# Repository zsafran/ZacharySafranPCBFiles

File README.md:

# ZacharySafranPCBFiles

The purpose of this repository is to showcase the PCB designs that I have worked with and those that I have created myself.

The folder 1_AntennaBrd_ANDESITE contains the .sch and .brd files for the antenna mounting PCB that I mention in my resume. I worked on designing this PCB with a research engineer in my lab. My main contributions to the design were to make sure that the mounting holes for the antennas, and sun sensor were in the right spot by referencing a CAD model of the satellite and to use MATLAB simulations to get an idea of how the shape of the PCB's ground plane would affect the monopole/dipole antennas's impedance.

The majority of the time I worked in the Space Technology Lab during the 2017 summer was spent on assembling and testing PCBs for the pico-satellite nodes that make up the ANDESITE satellite swarm. The .sch and .brd files for these PCBs are in the 2_Node_PCB_ANDESITE and 3_Node_SolarPanels_ANDESITE folders respectively. The main Node_PCB is a 4 layer PCB and the  Node_SolarPanels PCB is a 2 layer PCB. While I was not involved with designing either of these PCBs, working with them exposed me to more complex PCB layout and design techniques like using Restrict layer polygons to prevent ground plane copper from being laid in a specific area.

The only PCBs that I have designed and ordered completely by myself were two breakout boards for an altimeter sensor and an accelerometer sensor. I designed the altimeter PCB in EAGLE and the accelerometer PCB in Altium.

# Photos

## Satellite Pictures

<center></center>

A few of the full assembled satellite nodes.
&nbsp;

<center></center>

A partially assembled node satellite circuit board.
&nbsp;

## Testing Sensors Photo

<center></center>

My altimeter breakout board (top left) and my accelerometer breakout board (top right) can be see being tested in this picture.

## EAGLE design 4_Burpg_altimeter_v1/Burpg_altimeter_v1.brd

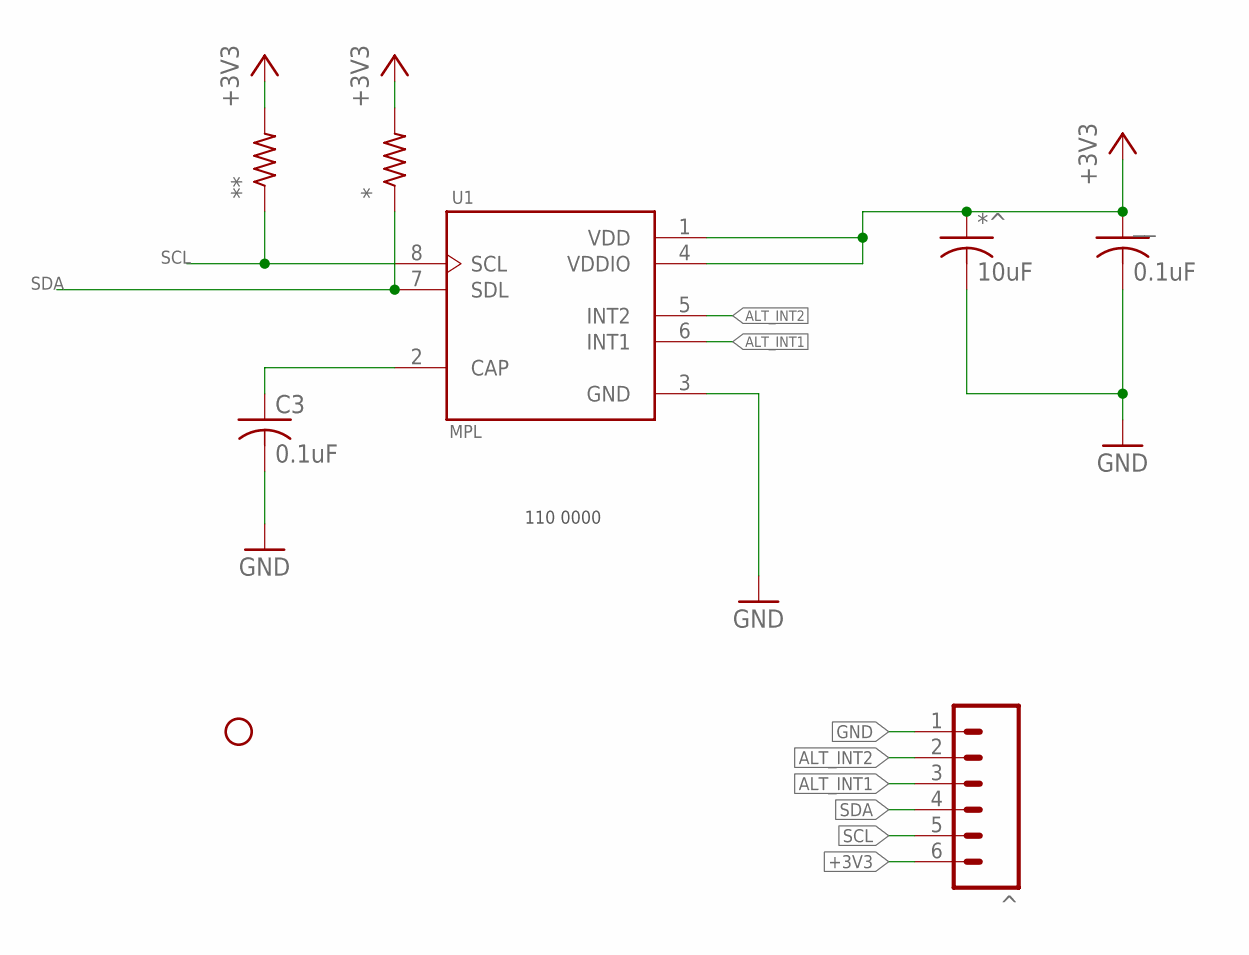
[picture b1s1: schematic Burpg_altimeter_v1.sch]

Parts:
*: R-US_R0603; R0603
**: R-US_R0603; R0603
*^: 10uF; C0603K
C3: 0.1uF; C0603K
U1: MPL; PSON125P300X500X120-8N
^: M06SILK_FEMALE_PTH; 1X06
_: #4_philip; STAND-OFF
__: 0.1uF; C0603K

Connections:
+3V3: *.2, **.2, *^.1, U1.1 (VDD), U1.4 (VDDIO), ^.6, __.1
ALT_INT1: U1.6 (INT1), ^.3
ALT_INT2: U1.5 (INT2), ^.2
GND: *^.2, C3.2, U1.3 (GND), ^.1, __.2
unnamed: C3.1, U1.2 (CAP)
SCL: **.1, U1.8 (SCL), ^.5
SDA: *.1, U1.7 (SDL), ^.4

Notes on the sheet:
110 0000

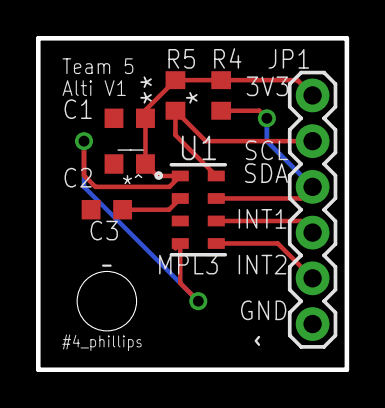
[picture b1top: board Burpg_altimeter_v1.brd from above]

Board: 2 copper layers, 17.1 x 18.4 mm, 8 parts (0 on the bottom side), 7 nets.

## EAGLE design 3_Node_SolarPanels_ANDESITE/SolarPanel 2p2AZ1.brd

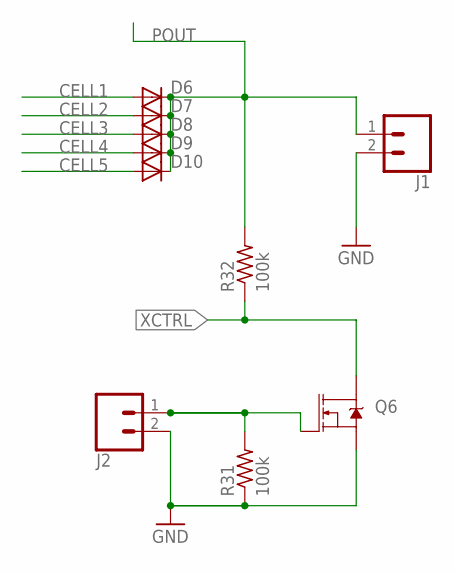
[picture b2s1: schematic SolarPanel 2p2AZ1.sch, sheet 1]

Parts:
D6, D7, D8, D9, D10: DIODE-SOD123; SOD123
J1, J2: CONN_02; 1X02
Q6: MOSFET-NCH-BSS138; SOT23-3
R31, R32: 100k; R0603

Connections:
CELL1: D6.A; also elsewhere on the board
CELL2: D7.A; also elsewhere on the board
CELL3: D8.A; also elsewhere on the board
CELL4: D9.A; also elsewhere on the board
CELL5: D10.A; also elsewhere on the board
GND: J1.2, J2.2, Q6.2 (S), R31.1; also elsewhere on the board
unnamed: J2.1, Q6.1 (G), R31.2
POUT: D6.C, D7.C, D8.C, D9.C, D10.C, J1.1, R32.2
XCTRL: Q6.3 (D), R32.1; also elsewhere on the board

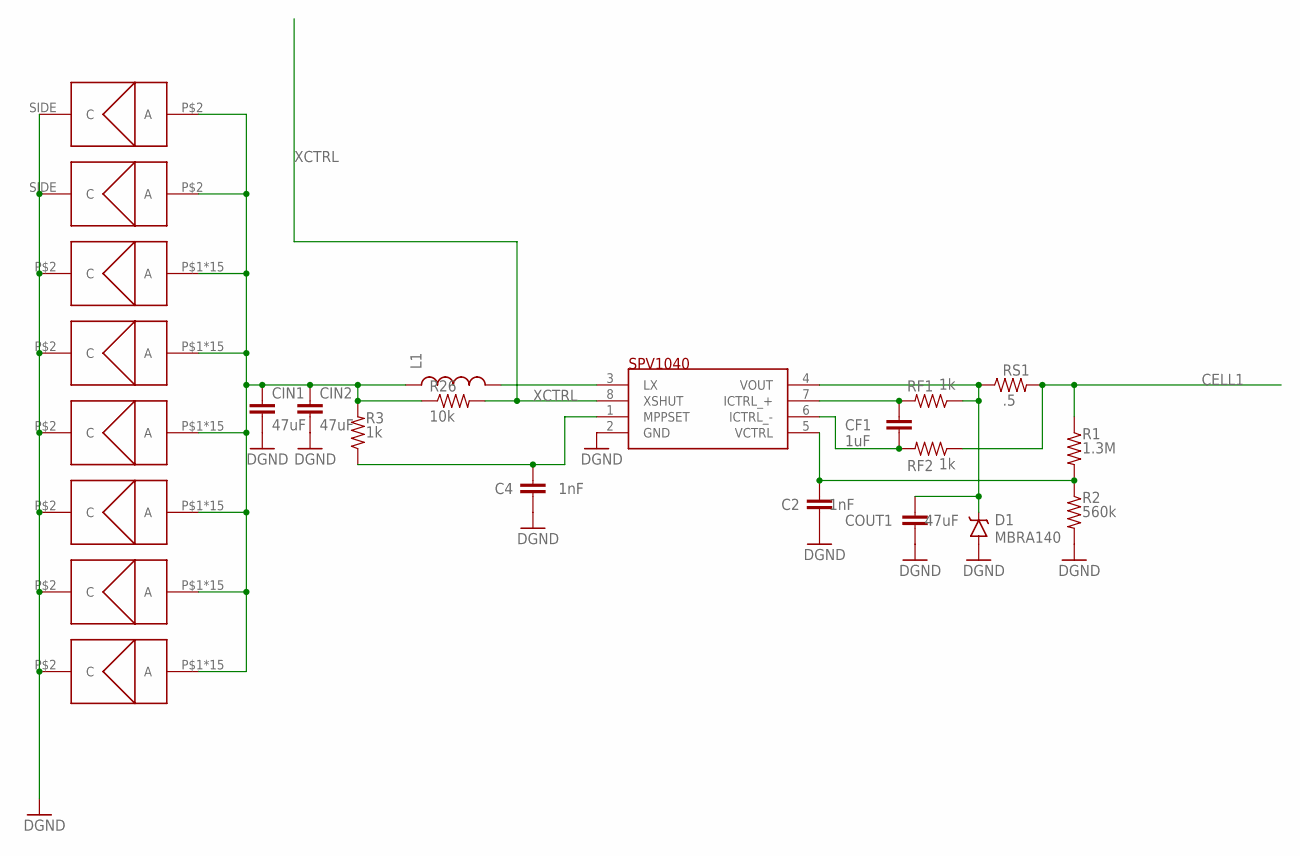
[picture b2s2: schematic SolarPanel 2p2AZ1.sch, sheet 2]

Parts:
C2, C4: 1nF; 0603-CAP
CF1: 1uF; 0603-CAP
CIN1, CIN2: 47uF; 1206
COUT1: 47uF; 1206
D1: MBRA140; SMA-DIODE
L1: INDUCTOR1210; 1210
R1: 1.3M; 0603-RES
R2: 560k; 0603-RES
R3: 1k; 0603-RES
R26: 10k; 0603-RES
RF1, RF2: 1k; 0603-RES
RS1: .5; 0603-RES
U$11, U$12, U$13, U$14, U$16, U$17: TASC_VIA
U$15: SPV1040; TSSOP8
U$18, U$19: TASC

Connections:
CELL1: R1.1, RF2.1, RS1.2; also elsewhere on the board
GND: C2.2, C4.2, CIN1.2, CIN2.2, COUT1.2, D1.A, R2.2, U$11.P$2 (C), U$12.P$2 (C), U$13.P$2 (C), U$14.P$2 (C), U$15.2 (GND), U$16.P$2 (C), U$17.P$2 (C), U$18.SIDE (C), U$19.SIDE (C); also elsewhere on the board
unnamed: CIN1.1, CIN2.1, L1.1, R3.2, R26.1, U$11.P$1 (A), U$11.P$3 (A), U$11.P$4 (A), U$11.P$5 (A), U$11.P$6 (A), U$11.P$7 (A), U$11.P$8 (A), U$11.P$9 (A), U$11.P$10 (A), U$11.P$11 (A), U$11.P$12 (A), U$11.P$13 (A), U$11.P$14 (A), U$11.P$15 (A), U$11.P$16 (A), U$12.P$1 (A), U$12.P$3 (A), U$12.P$4 (A), U$12.P$5 (A), U$12.P$6 (A), U$12.P$7 (A), U$12.P$8 (A), U$12.P$9 (A), U$12.P$10 (A), U$12.P$11 (A), U$12.P$12 (A), U$12.P$13 (A), U$12.P$14 (A), U$12.P$15 (A), U$12.P$16 (A), U$13.P$1 (A), U$13.P$3 (A), U$13.P$4 (A), U$13.P$5 (A), U$13.P$6 (A), U$13.P$7 (A), U$13.P$8 (A), U$13.P$9 (A), U$13.P$10 (A), U$13.P$11 (A), U$13.P$12 (A), U$13.P$13 (A), U$13.P$14 (A), U$13.P$15 (A), U$13.P$16 (A), U$14.P$1 (A), U$14.P$3 (A), U$14.P$4 (A), U$14.P$5 (A), U$14.P$6 (A), U$14.P$7 (A), U$14.P$8 (A), U$14.P$9 (A), U$14.P$10 (A), U$14.P$11 (A), U$14.P$12 (A), U$14.P$13 (A), U$14.P$14 (A), U$14.P$15 (A), U$14.P$16 (A), U$16.P$1 (A), U$16.P$3 (A), U$16.P$4 (A), U$16.P$5 (A), U$16.P$6 (A), U$16.P$7 (A), U$16.P$8 (A), U$16.P$9 (A), U$16.P$10 (A), U$16.P$11 (A), U$16.P$12 (A), U$16.P$13 (A), U$16.P$14 (A), U$16.P$15 (A), U$16.P$16 (A), U$17.P$1 (A), U$17.P$3 (A), U$17.P$4 (A), U$17.P$5 (A), U$17.P$6 (A), U$17.P$7 (A), U$17.P$8 (A), U$17.P$9 (A), U$17.P$10 (A), U$17.P$11 (A), U$17.P$12 (A), U$17.P$13 (A), U$17.P$14 (A), U$17.P$15 (A), U$17.P$16 (A), U$18.P$2 (A), U$19.P$2 (A)
unnamed: C2.1, R1.2, R2.1, U$15.5 (VCTRL)
unnamed: CF1.1, RF1.2, U$15.7 (ICTRL_+)
unnamed: CF1.2, RF2.2, U$15.6 (ICTRL_-)
unnamed: COUT1.1, D1.C, RF1.1, RS1.1, U$15.4 (VOUT)
unnamed: L1.2, U$15.3 (LX)
unnamed: C4.1, R3.1, U$15.1 (MPPSET)
XCTRL: R26.2, U$15.8 (XSHUT); also elsewhere on the board

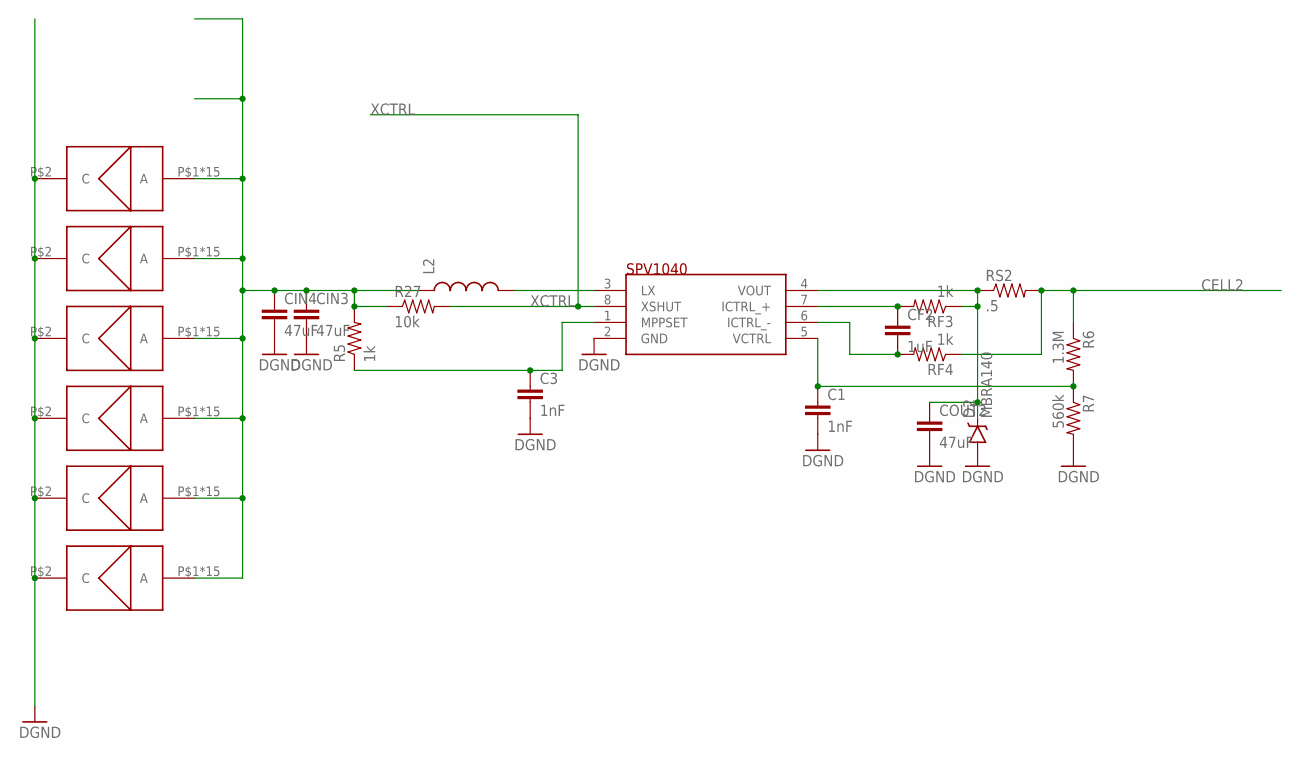
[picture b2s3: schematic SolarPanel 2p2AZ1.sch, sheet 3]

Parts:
C1, C3: 1nF; 0603-CAP
CF2: 1uF; 0603-CAP
CIN3, CIN4: 47uF; 1206
COUT2: 47uF; 1206
D2: MBRA140; SMA-DIODE
L2: INDUCTOR1210; 1210
R5: 1k; 0603-RES
R6: 1.3M; 0603-RES
R7: 560k; 0603-RES
R27: 10k; 0603-RES
RF3, RF4: 1k; 0603-RES
RS2: .5; 0603-RES
U$1, U$2, U$3, U$4, U$6, U$7: TASC_VIA
U$5: SPV1040; TSSOP8

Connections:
CELL2: R6.1, RF4.1, RS2.2; also elsewhere on the board
GND: C1.2, C3.2, CIN3.2, CIN4.2, COUT2.2, D2.A, R7.2, U$1.P$2 (C), U$2.P$2 (C), U$3.P$2 (C), U$4.P$2 (C), U$5.2 (GND), U$6.P$2 (C), U$7.P$2 (C); also elsewhere on the board
unnamed: CIN3.1, CIN4.1, L2.1, R5.2, R27.1, U$1.P$1 (A), U$1.P$3 (A), U$1.P$4 (A), U$1.P$5 (A), U$1.P$6 (A), U$1.P$7 (A), U$1.P$8 (A), U$1.P$9 (A), U$1.P$10 (A), U$1.P$11 (A), U$1.P$12 (A), U$1.P$13 (A), U$1.P$14 (A), U$1.P$15 (A), U$1.P$16 (A), U$2.P$1 (A), U$2.P$3 (A), U$2.P$4 (A), U$2.P$5 (A), U$2.P$6 (A), U$2.P$7 (A), U$2.P$8 (A), U$2.P$9 (A), U$2.P$10 (A), U$2.P$11 (A), U$2.P$12 (A), U$2.P$13 (A), U$2.P$14 (A), U$2.P$15 (A), U$2.P$16 (A), U$3.P$1 (A), U$3.P$3 (A), U$3.P$4 (A), U$3.P$5 (A), U$3.P$6 (A), U$3.P$7 (A), U$3.P$8 (A), U$3.P$9 (A), U$3.P$10 (A), U$3.P$11 (A), U$3.P$12 (A), U$3.P$13 (A), U$3.P$14 (A), U$3.P$15 (A), U$3.P$16 (A), U$4.P$1 (A), U$4.P$3 (A), U$4.P$4 (A), U$4.P$5 (A), U$4.P$6 (A), U$4.P$7 (A), U$4.P$8 (A), U$4.P$9 (A), U$4.P$10 (A), U$4.P$11 (A), U$4.P$12 (A), U$4.P$13 (A), U$4.P$14 (A), U$4.P$15 (A), U$4.P$16 (A), U$6.P$1 (A), U$6.P$3 (A), U$6.P$4 (A), U$6.P$5 (A), U$6.P$6 (A), U$6.P$7 (A), U$6.P$8 (A), U$6.P$9 (A), U$6.P$10 (A), U$6.P$11 (A), U$6.P$12 (A), U$6.P$13 (A), U$6.P$14 (A), U$6.P$15 (A), U$6.P$16 (A), U$7.P$1 (A), U$7.P$3 (A), U$7.P$4 (A), U$7.P$5 (A), U$7.P$6 (A), U$7.P$7 (A), U$7.P$8 (A), U$7.P$9 (A), U$7.P$10 (A), U$7.P$11 (A), U$7.P$12 (A), U$7.P$13 (A), U$7.P$14 (A), U$7.P$15 (A), U$7.P$16 (A)
unnamed: C3.1, R5.1, U$5.1 (MPPSET)
unnamed: C1.1, R6.2, R7.1, U$5.5 (VCTRL)
unnamed: CF2.1, RF3.2, U$5.7 (ICTRL_+)
unnamed: CF2.2, RF4.2, U$5.6 (ICTRL_-)
unnamed: COUT2.1, D2.C, RF3.1, RS2.1, U$5.4 (VOUT)
unnamed: L2.2, U$5.3 (LX)
XCTRL: R27.2, U$5.8 (XSHUT); also elsewhere on the board

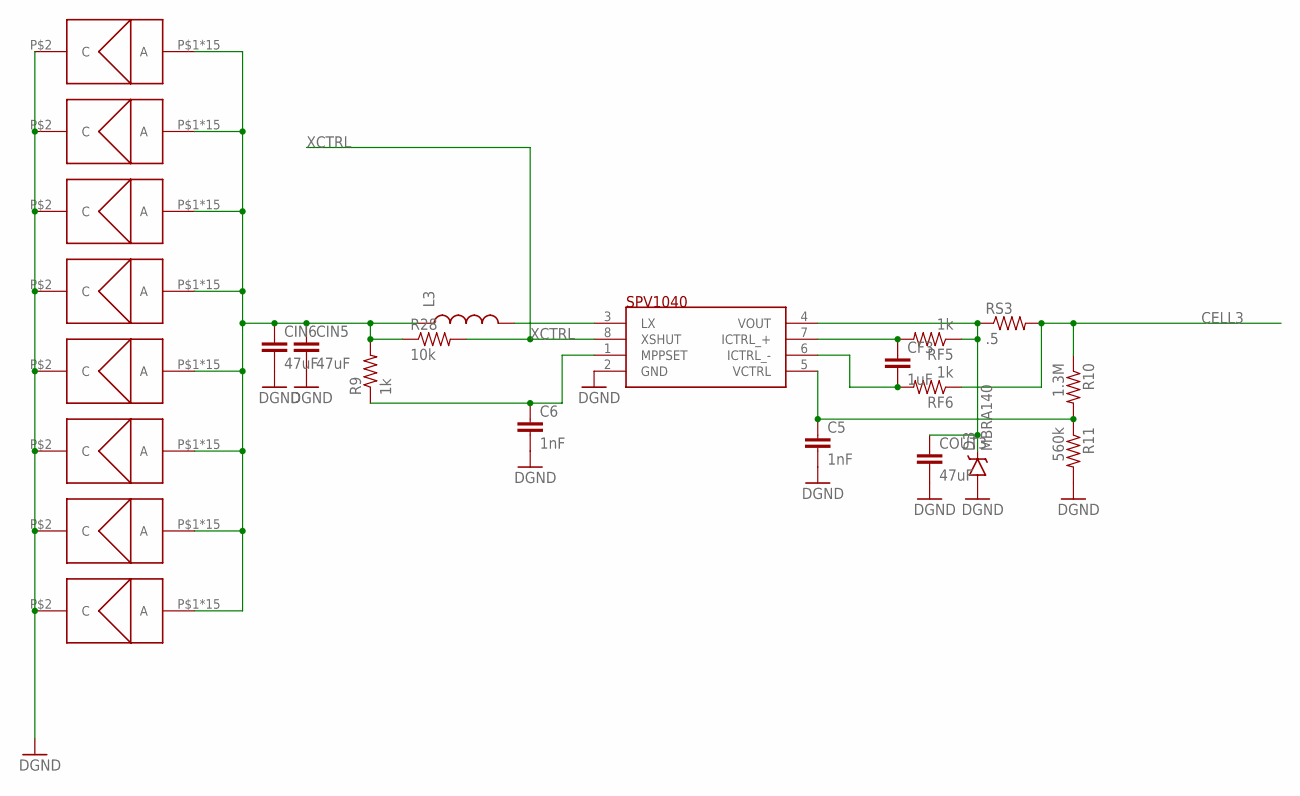
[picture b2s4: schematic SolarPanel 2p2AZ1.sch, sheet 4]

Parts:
C5, C6: 1nF; 0603-CAP
CF3: 1uF; 0603-CAP
CIN5, CIN6: 47uF; 1206
COUT3: 47uF; 1206
D3: MBRA140; SMA-DIODE
L3: INDUCTOR1210; 1210
R9: 1k; 0603-RES
R10: 1.3M; 0603-RES
R11: 560k; 0603-RES
R28: 10k; 0603-RES
RF5, RF6: 1k; 0603-RES
RS3: .5; 0603-RES
U$21, U$22, U$23, U$24, U$26, U$27, U$28, U$29: TASC_VIA
U$25: SPV1040; TSSOP8

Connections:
CELL3: R10.1, RF6.1, RS3.2; also elsewhere on the board
GND: C5.2, C6.2, CIN5.2, CIN6.2, COUT3.2, D3.A, R11.2, U$21.P$2 (C), U$22.P$2 (C), U$23.P$2 (C), U$24.P$2 (C), U$25.2 (GND), U$26.P$2 (C), U$27.P$2 (C), U$28.P$2 (C), U$29.P$2 (C); also elsewhere on the board
unnamed: CIN5.1, CIN6.1, L3.1, R9.2, R28.1, U$21.P$1 (A), U$21.P$3 (A), U$21.P$4 (A), U$21.P$5 (A), U$21.P$6 (A), U$21.P$7 (A), U$21.P$8 (A), U$21.P$9 (A), U$21.P$10 (A), U$21.P$11 (A), U$21.P$12 (A), U$21.P$13 (A), U$21.P$14 (A), U$21.P$15 (A), U$21.P$16 (A), U$22.P$1 (A), U$22.P$3 (A), U$22.P$4 (A), U$22.P$5 (A), U$22.P$6 (A), U$22.P$7 (A), U$22.P$8 (A), U$22.P$9 (A), U$22.P$10 (A), U$22.P$11 (A), U$22.P$12 (A), U$22.P$13 (A), U$22.P$14 (A), U$22.P$15 (A), U$22.P$16 (A), U$23.P$1 (A), U$23.P$3 (A), U$23.P$4 (A), U$23.P$5 (A), U$23.P$6 (A), U$23.P$7 (A), U$23.P$8 (A), U$23.P$9 (A), U$23.P$10 (A), U$23.P$11 (A), U$23.P$12 (A), U$23.P$13 (A), U$23.P$14 (A), U$23.P$15 (A), U$23.P$16 (A), U$24.P$1 (A), U$24.P$3 (A), U$24.P$4 (A), U$24.P$5 (A), U$24.P$6 (A), U$24.P$7 (A), U$24.P$8 (A), U$24.P$9 (A), U$24.P$10 (A), U$24.P$11 (A), U$24.P$12 (A), U$24.P$13 (A), U$24.P$14 (A), U$24.P$15 (A), U$24.P$16 (A), U$26.P$1 (A), U$26.P$3 (A), U$26.P$4 (A), U$26.P$5 (A), U$26.P$6 (A), U$26.P$7 (A), U$26.P$8 (A), U$26.P$9 (A), U$26.P$10 (A), U$26.P$11 (A), U$26.P$12 (A), U$26.P$13 (A), U$26.P$14 (A), U$26.P$15 (A), U$26.P$16 (A), U$27.P$1 (A), U$27.P$3 (A), U$27.P$4 (A), U$27.P$5 (A), U$27.P$6 (A), U$27.P$7 (A), U$27.P$8 (A), U$27.P$9 (A), U$27.P$10 (A), U$27.P$11 (A), U$27.P$12 (A), U$27.P$13 (A), U$27.P$14 (A), U$27.P$15 (A), U$27.P$16 (A), U$28.P$1 (A), U$28.P$3 (A), U$28.P$4 (A), U$28.P$5 (A), U$28.P$6 (A), U$28.P$7 (A), U$28.P$8 (A), U$28.P$9 (A), U$28.P$10 (A), U$28.P$11 (A), U$28.P$12 (A), U$28.P$13 (A), U$28.P$14 (A), U$28.P$15 (A), U$28.P$16 (A), U$29.P$1 (A), U$29.P$3 (A), U$29.P$4 (A), U$29.P$5 (A), U$29.P$6 (A), U$29.P$7 (A), U$29.P$8 (A), U$29.P$9 (A), U$29.P$10 (A), U$29.P$11 (A), U$29.P$12 (A), U$29.P$13 (A), U$29.P$14 (A), U$29.P$15 (A), U$29.P$16 (A)
unnamed: C6.1, R9.1, U$25.1 (MPPSET)
unnamed: C5.1, R10.2, R11.1, U$25.5 (VCTRL)
unnamed: CF3.1, RF5.2, U$25.7 (ICTRL_+)
unnamed: CF3.2, RF6.2, U$25.6 (ICTRL_-)
unnamed: COUT3.1, D3.C, RF5.1, RS3.1, U$25.4 (VOUT)
unnamed: L3.2, U$25.3 (LX)
XCTRL: R28.2, U$25.8 (XSHUT); also elsewhere on the board

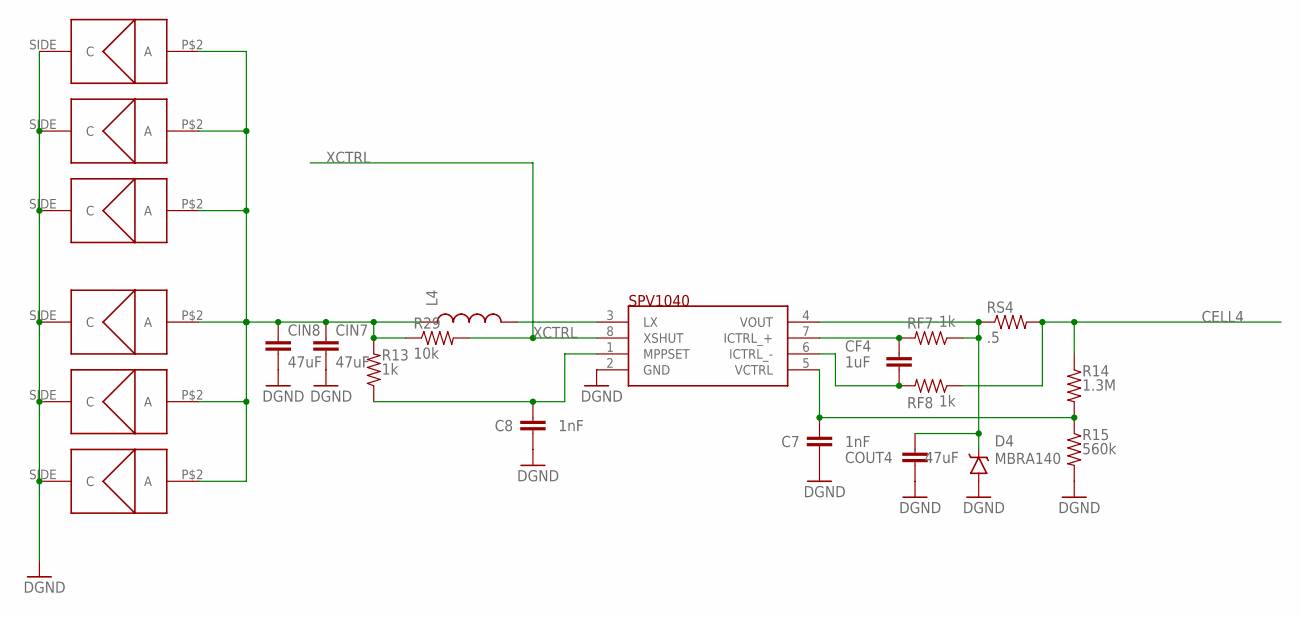
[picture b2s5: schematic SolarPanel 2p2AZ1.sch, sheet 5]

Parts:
C7, C8: 1nF; 0603-CAP
CF4: 1uF; 0603-CAP
CIN7, CIN8: 47uF; 1206
COUT4: 47uF; 1206
D4: MBRA140; SMA-DIODE
L4: INDUCTOR1210; 1210
R13: 1k; 0603-RES
R14: 1.3M; 0603-RES
R15: 560k; 0603-RES
R29: 10k; 0603-RES
RF7, RF8: 1k; 0603-RES
RS4: .5; 0603-RES
U$33, U$34, U$36, U$37, U$38, U$39: TASC
U$35: SPV1040; TSSOP8

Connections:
CELL4: R14.1, RF8.1, RS4.2; also elsewhere on the board
GND: C7.2, C8.2, CIN7.2, CIN8.2, COUT4.2, D4.A, R15.2, U$33.SIDE (C), U$34.SIDE (C), U$35.2 (GND), U$36.SIDE (C), U$37.SIDE (C), U$38.SIDE (C), U$39.SIDE (C); also elsewhere on the board
unnamed: CIN7.1, CIN8.1, L4.1, R13.2, R29.1, U$33.P$2 (A), U$34.P$2 (A), U$36.P$2 (A), U$37.P$2 (A), U$38.P$2 (A), U$39.P$2 (A)
unnamed: C8.1, R13.1, U$35.1 (MPPSET)
unnamed: C7.1, R14.2, R15.1, U$35.5 (VCTRL)
unnamed: CF4.1, RF7.2, U$35.7 (ICTRL_+)
unnamed: CF4.2, RF8.2, U$35.6 (ICTRL_-)
unnamed: COUT4.1, D4.C, RF7.1, RS4.1, U$35.4 (VOUT)
unnamed: L4.2, U$35.3 (LX)
XCTRL: R29.2, U$35.8 (XSHUT); also elsewhere on the board

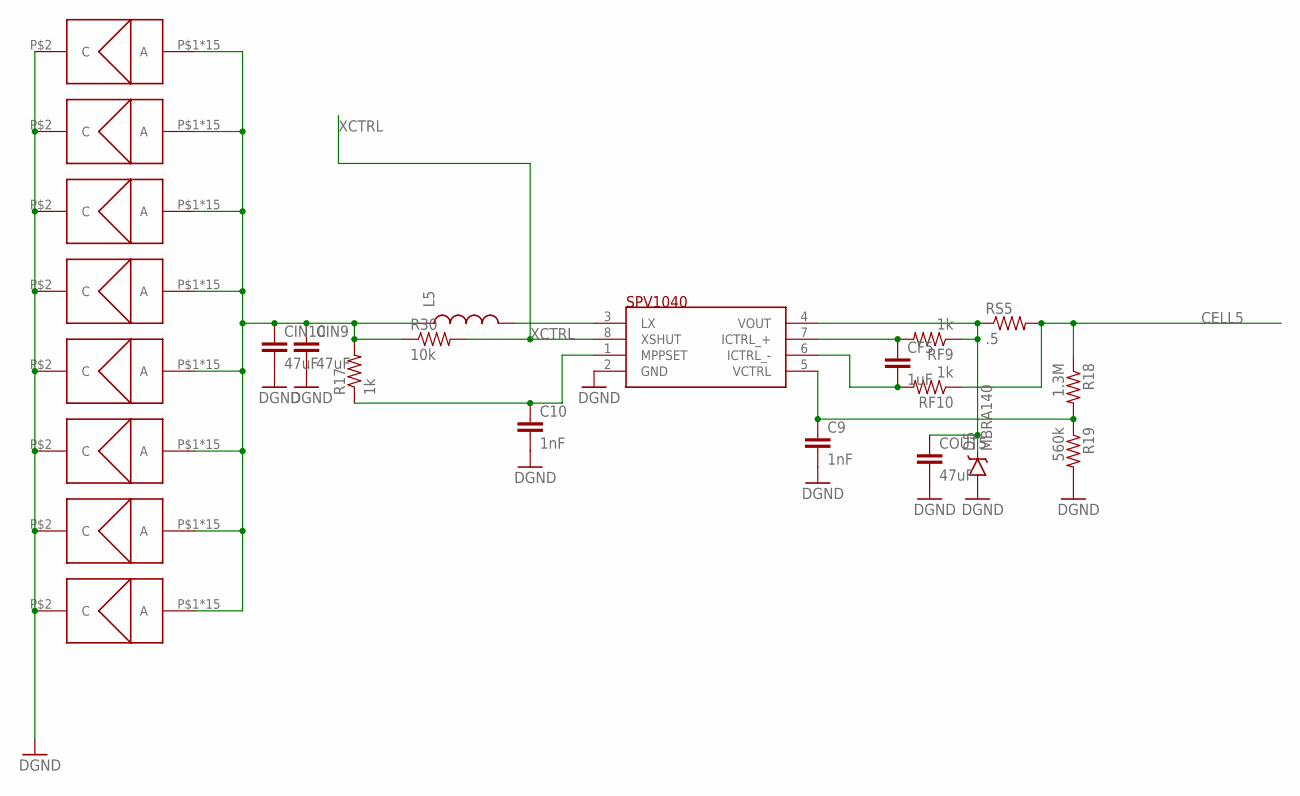
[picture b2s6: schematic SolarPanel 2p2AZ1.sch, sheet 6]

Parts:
C9, C10: 1nF; 0603-CAP
CF5: 1uF; 0603-CAP
CIN9, CIN10: 47uF; 1206
COUT5: 47uF; 1206
D5: MBRA140; SMA-DIODE
L5: INDUCTOR1210; 1210
R17: 1k; 0603-RES
R18: 1.3M; 0603-RES
R19: 560k; 0603-RES
R30: 10k; 0603-RES
RF9, RF10: 1k; 0603-RES
RS5: .5; 0603-RES
U$41, U$42, U$43, U$44, U$46, U$47, U$48, U$49: TASC_VIA
U$45: SPV1040; TSSOP8

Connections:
CELL5: R18.1, RF10.1, RS5.2; also elsewhere on the board
GND: C9.2, C10.2, CIN9.2, CIN10.2, COUT5.2, D5.A, R19.2, U$41.P$2 (C), U$42.P$2 (C), U$43.P$2 (C), U$44.P$2 (C), U$45.2 (GND), U$46.P$2 (C), U$47.P$2 (C), U$48.P$2 (C), U$49.P$2 (C); also elsewhere on the board
unnamed: CIN9.1, CIN10.1, L5.1, R17.2, R30.1, U$41.P$1 (A), U$41.P$3 (A), U$41.P$4 (A), U$41.P$5 (A), U$41.P$6 (A), U$41.P$7 (A), U$41.P$8 (A), U$41.P$9 (A), U$41.P$10 (A), U$41.P$11 (A), U$41.P$12 (A), U$41.P$13 (A), U$41.P$14 (A), U$41.P$15 (A), U$41.P$16 (A), U$42.P$1 (A), U$42.P$3 (A), U$42.P$4 (A), U$42.P$5 (A), U$42.P$6 (A), U$42.P$7 (A), U$42.P$8 (A), U$42.P$9 (A), U$42.P$10 (A), U$42.P$11 (A), U$42.P$12 (A), U$42.P$13 (A), U$42.P$14 (A), U$42.P$15 (A), U$42.P$16 (A), U$43.P$1 (A), U$43.P$3 (A), U$43.P$4 (A), U$43.P$5 (A), U$43.P$6 (A), U$43.P$7 (A), U$43.P$8 (A), U$43.P$9 (A), U$43.P$10 (A), U$43.P$11 (A), U$43.P$12 (A), U$43.P$13 (A), U$43.P$14 (A), U$43.P$15 (A), U$43.P$16 (A), U$44.P$1 (A), U$44.P$3 (A), U$44.P$4 (A), U$44.P$5 (A), U$44.P$6 (A), U$44.P$7 (A), U$44.P$8 (A), U$44.P$9 (A), U$44.P$10 (A), U$44.P$11 (A), U$44.P$12 (A), U$44.P$13 (A), U$44.P$14 (A), U$44.P$15 (A), U$44.P$16 (A), U$46.P$1 (A), U$46.P$3 (A), U$46.P$4 (A), U$46.P$5 (A), U$46.P$6 (A), U$46.P$7 (A), U$46.P$8 (A), U$46.P$9 (A), U$46.P$10 (A), U$46.P$11 (A), U$46.P$12 (A), U$46.P$13 (A), U$46.P$14 (A), U$46.P$15 (A), U$46.P$16 (A), U$47.P$1 (A), U$47.P$3 (A), U$47.P$4 (A), U$47.P$5 (A), U$47.P$6 (A), U$47.P$7 (A), U$47.P$8 (A), U$47.P$9 (A), U$47.P$10 (A), U$47.P$11 (A), U$47.P$12 (A), U$47.P$13 (A), U$47.P$14 (A), U$47.P$15 (A), U$47.P$16 (A), U$48.P$1 (A), U$48.P$3 (A), U$48.P$4 (A), U$48.P$5 (A), U$48.P$6 (A), U$48.P$7 (A), U$48.P$8 (A), U$48.P$9 (A), U$48.P$10 (A), U$48.P$11 (A), U$48.P$12 (A), U$48.P$13 (A), U$48.P$14 (A), U$48.P$15 (A), U$48.P$16 (A), U$49.P$1 (A), U$49.P$3 (A), U$49.P$4 (A), U$49.P$5 (A), U$49.P$6 (A), U$49.P$7 (A), U$49.P$8 (A), U$49.P$9 (A), U$49.P$10 (A), U$49.P$11 (A), U$49.P$12 (A), U$49.P$13 (A), U$49.P$14 (A), U$49.P$15 (A), U$49.P$16 (A)
unnamed: C10.1, R17.1, U$45.1 (MPPSET)
unnamed: C9.1, R18.2, R19.1, U$45.5 (VCTRL)
unnamed: CF5.1, RF9.2, U$45.7 (ICTRL_+)
unnamed: CF5.2, RF10.2, U$45.6 (ICTRL_-)
unnamed: COUT5.1, D5.C, RF9.1, RS5.1, U$45.4 (VOUT)
unnamed: L5.2, U$45.3 (LX)
XCTRL: R30.2, U$45.8 (XSHUT); also elsewhere on the board

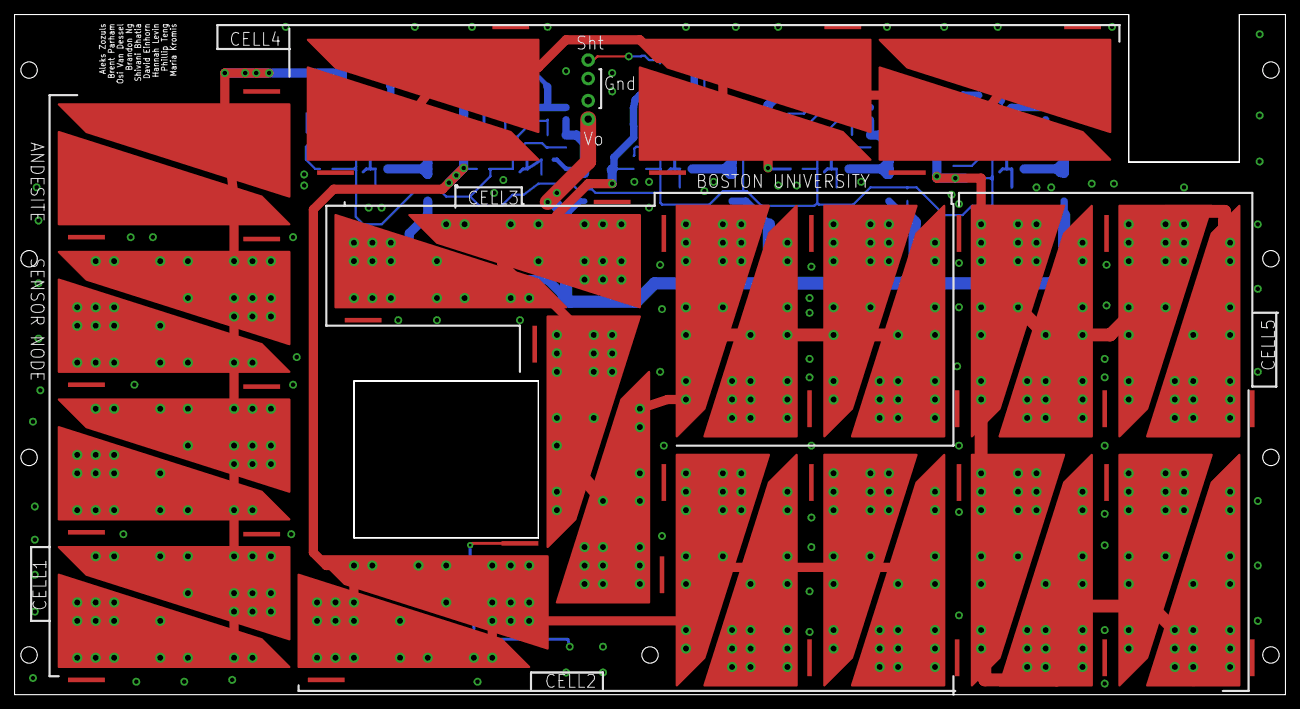
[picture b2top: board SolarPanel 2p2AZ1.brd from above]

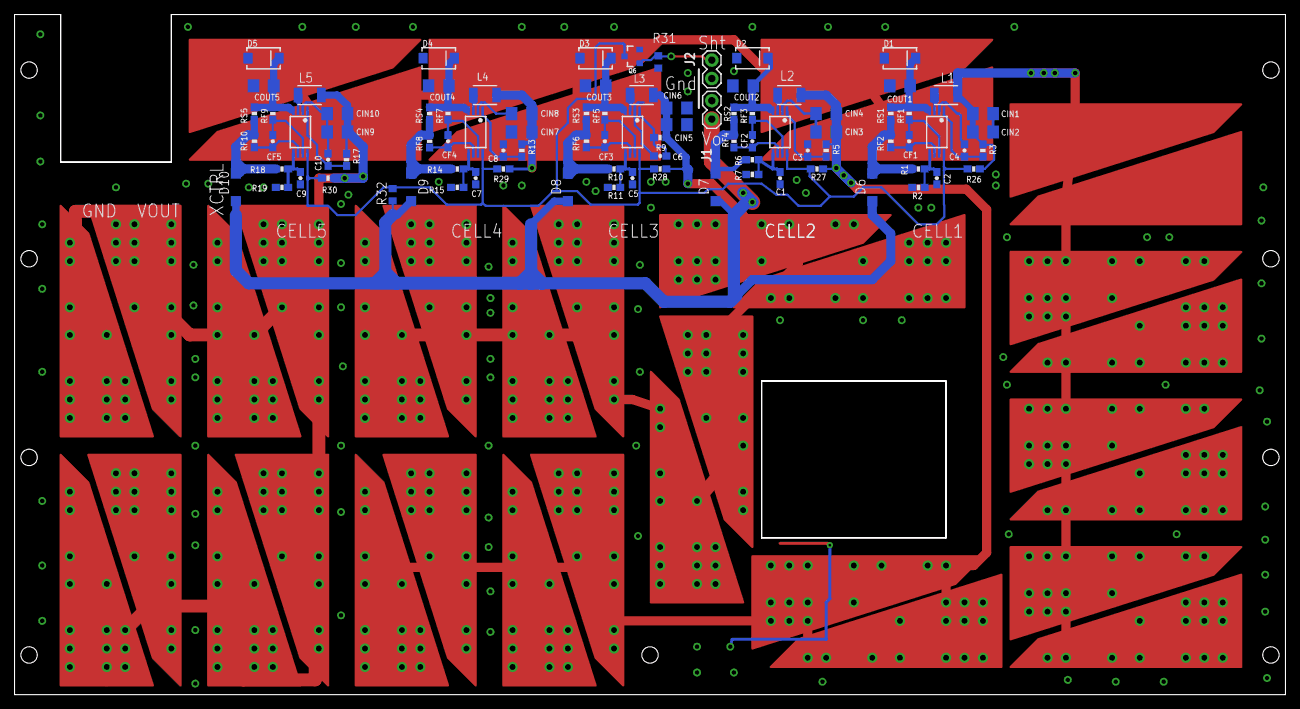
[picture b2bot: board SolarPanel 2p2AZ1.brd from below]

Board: 2 copper layers, 175.0 x 93.6 mm, 126 parts (90 on the bottom side), 44 nets.

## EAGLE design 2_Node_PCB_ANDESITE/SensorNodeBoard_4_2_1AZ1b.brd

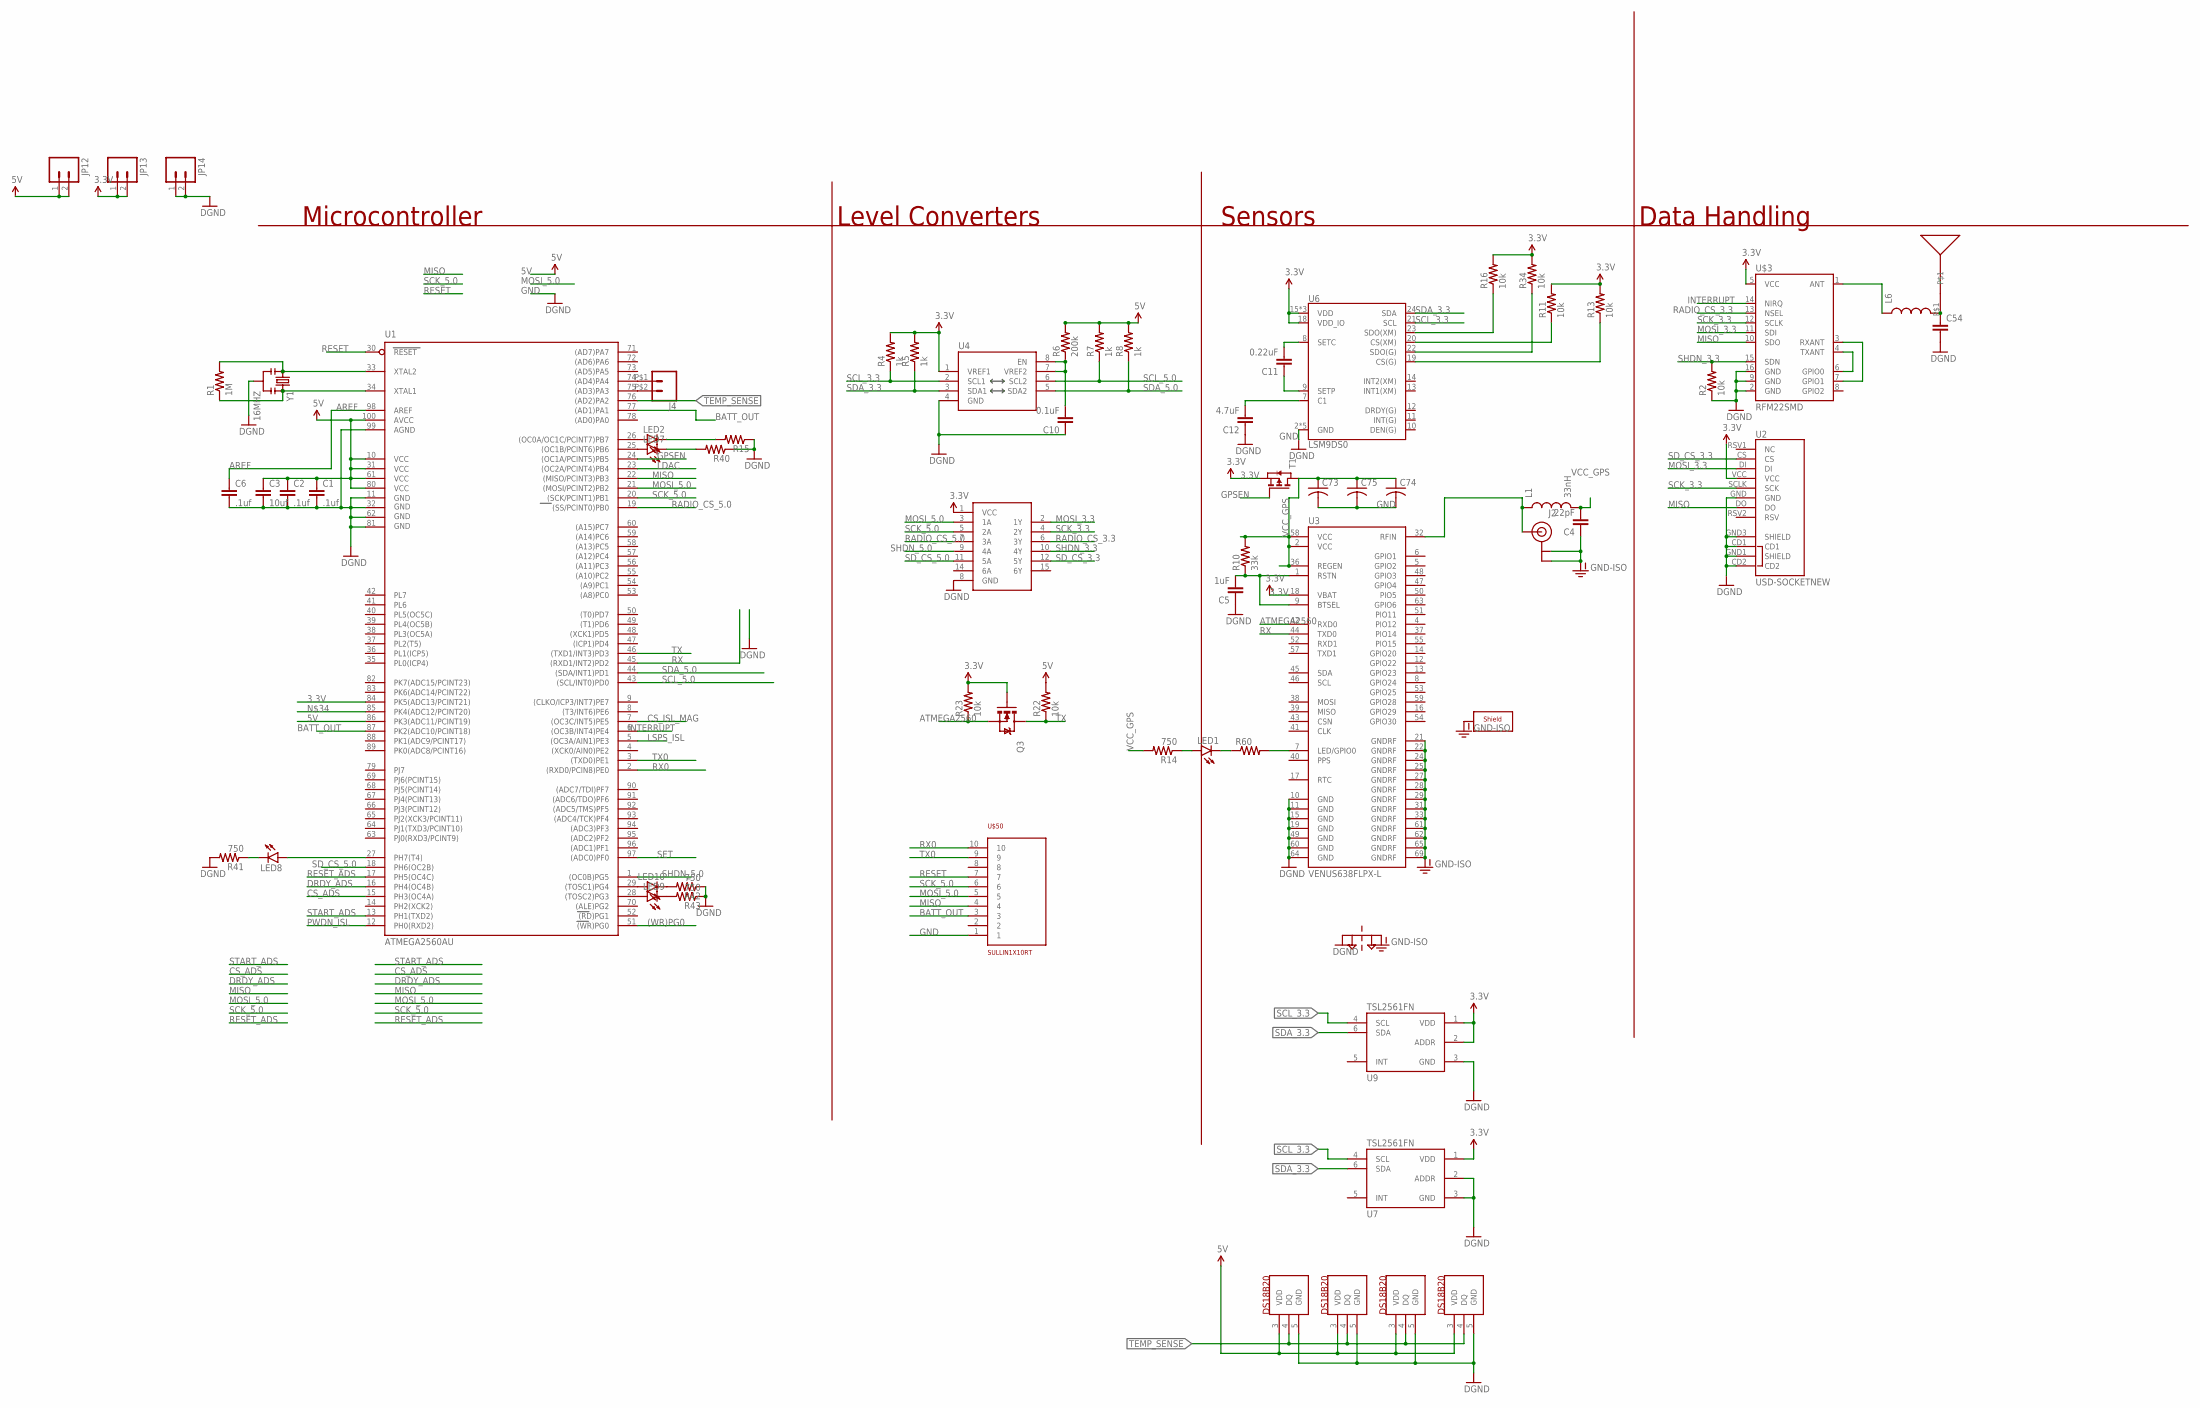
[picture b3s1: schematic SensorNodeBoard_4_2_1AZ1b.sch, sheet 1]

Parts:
C1, C2, C6: .1uf; 0603-CAP
C3: 10uf; 0603-CAP
C4: 22pF; 0603-CAP
C5: 1uF; 0603-CAP
C10: 0.1uF; 0603-CAP
C11: 0.22uF; 0603-CAP
C12: 4.7uF; 0603-CAP
C54: CAP0603-CAP; 0603-CAP
C73, C74, C75: C-USC0603K; C0603K
J2: U.FL
J4: CONN_02HIROSE; 1X02_1.25
JP12, JP13, JP14: M02LOCK; 1X02_LOCK
L1: 33nH; 0805
L6: INDUCTOR0805; 0805
LED1, LED2, LED7, LED8, LED9, LED10: LED0603; LED-0603
PT1: 2PT_GND_TIE
Q3: MOSFET-NCHANNEL2N7002PW; SOT323
R1: 1M; R1206
R2, R11, R13, R16, R22, R23, R34: 10k; 0603-RES
R4, R5, R7, R8: 1k; 0603-RES
R6: 200k; 0603-RES
R10: 33k; 0603-RES
R14, R41, R42, R43: 750; 0603-RES
R15, R40: RESISTOR0603-RES; 0603-RES
R60: R-US_R0603; R0603
T1: PMOSSOT23-6; SOT23-6
U1: ATMEGA2560AU; TQFP100
U2: USD-SOCKETNEW; MICRO-SD-SOCKET-PP
U3: VENUS638FLPX-L; VENUS638FLPX
U4: PCA9306; PSOP-8
U6: LSM9DS0; LGA-24
U7, U9: TSL2561FN; FN-6
U$1: 74HC4050; TSSOP16
U$3: RFM22SMD; RFM22-XXX-S2
U$23: SNB_ANT; SLOT
U$24, U$25, U$47, U$48: DS18B202; SO08
U$50: SULLIN1X10RT; SULLRT1X10-2MM
U$52: SHEILD3; SHIELD_BMI-201-C-REV
Y1: 16MHZ; RESONATOR-SMD

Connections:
3.3V: JP13.1, JP13.2, Q3.1 (G), R4.2, R5.2, R11.2, R13.2, R16.2, R23.2, R34.2, T1.4 (S), U1.84 (PK5(ADC13/PCINT21)), U2.VCC, U3.18 (VBAT), U4.1 (VREF1), U6.15 (VDD), U6.16 (VDD), U6.17 (VDD), U6.18 (VDD_IO), U7.1 (VDD), U9.1 (VDD), U9.2 (ADDR), U$1.1 (VCC), U$3.5 (VCC); also elsewhere on the board
5V: C1.1, C2.1, C3.1, JP12.1, JP12.2, R6.2, R7.2, R8.2, R22.2, U1.10 (VCC), U1.31 (VCC1), U1.61 (VCC2), U1.80 (VCC3), U1.86 (PK3(ADC11/PCINT19)), U1.100 (AVCC), U$24.3 (VDD), U$25.3 (VDD), U$47.3 (VDD), U$48.3 (VDD); also elsewhere on the board
(WR)PG0: U1.51 ((WR)PG0)
AREF: C6.1, U1.98 (AREF)
ATMEGA2560: Q3.2 (S), R23.1, U3.42 (RXD0)
BATT_OUT: U1.77 ((AD1)PA1), U1.87 (PK2(ADC10/PCINT18)), U$50.3; also elsewhere on the board
CS_ADS: U1.15 (PH3(OC4A)); also elsewhere on the board
CS_ISL_MAG: U1.7 ((OC3C/INT5)PE5)
DRDY_ADS: U1.16 (PH4(OC4B)); also elsewhere on the board
GND: C1.2, C2.2, C3.2, C5.1, C6.2, C10.1, C12.1, C54.2, C73.2, C74.2, C75.2, JP14.1, JP14.2, PT1.P$1, R2.1, R15.1, R40.1, R41.2, R42.1, R43.1, U1.11 (GND), U1.32 (GND1), U1.62 (GND2), U1.81 (GND3), U1.99 (AGND), U2.CD1, U2.CD2, U2.GND, U2.GND1 (SHIELD), U2.GND3 (SHIELD), U3.10 (GND), U3.11 (GND), U3.15 (GND), U3.19 (GND), U3.49 (GND), U3.60 (GND), U3.64 (GND), U4.4 (GND), U6.2 (GND), U6.3 (GND), U6.4 (GND), U6.5 (GND), U6.6 (GND), U7.2 (ADDR), U7.3 (GND), U9.3 (GND), U$1.8 (GND), U$3.2 (GND), U$3.9 (GND), U$3.16 (GND), U$24.5 (GND), U$25.5 (GND), U$47.5 (GND), U$48.5 (GND), U$50.1, Y1.2; also elsewhere on the board
GND-ISO: C4.1, J2.P$1 (GND), J2.P$2 (GND), PT1.P$2, U3.21 (GNDRF), U3.22 (GNDRF), U3.24 (GNDRF), U3.25 (GNDRF), U3.27 (GNDRF), U3.28 (GNDRF), U3.29 (GNDRF), U3.31 (GNDRF), U3.33 (GNDRF), U3.61 (GNDRF), U3.62 (GNDRF), U3.65 (GNDRF), U3.69 (GNDRF), U$52.P$1, U$52.P$2, U$52.P$3, U$52.P$4, U$52.P$5, U$52.P$6, U$52.P$7, U$52.P$8, U$52.P$9
GPSEN: T1.3 (G), U1.24 ((OC1A/PCINT5)PB5)
INTERRUPT: U1.6 ((OC3B/INT4)PE4), U$3.14 (NIRQ)
LDAC: U1.23 ((OC2A/PCINT4)PB4)
LSPS_ISL: U1.5 ((OC3A/AIN1)PE3)
MISO: U1.22 ((MISO/PCINT3)PB3), U2.DO, U$3.10 (SDO), U$50.4; also elsewhere on the board
MOSI_3.3: U2.DI, U$1.2 (1Y), U$3.11 (SDI)
MOSI_5.0: U1.21 ((MOSI/PCINT2)PB2), U$1.3 (1A), U$50.5; also elsewhere on the board
unnamed: C11.1, U6.9 (SETP)
unnamed: J2.P$3 (SIGNAL), L1.1, U3.32 (RFIN)
unnamed: R1.1, U1.34 (XTAL1), Y1.3
unnamed: R1.2, U1.33 (XTAL2), Y1.1
unnamed: C10.2, R6.1, U4.7 (VREF2), U4.8 (EN)
unnamed: U$3.4 (TXANT), U$3.6 (GPIO0)
unnamed: U$3.3 (RXANT), U$3.7 (GPIO1)
unnamed: C11.2, U6.8 (SETC)
unnamed: C12.2, U6.7 (C1)
unnamed: LED2.A, U1.26 ((OC0A/OC1C/PCINT7)PB7)
unnamed: R11.1, U6.20 (CS(XM))
unnamed: R13.1, U6.19 (CS(G))
unnamed: J4.P$1 (1), U1.74 ((AD4)PA4)
unnamed: J4.P$2 (2), U1.75 ((AD3)PA3)
unnamed: C5.2, R10.1, U3.1 (RSTN), U3.9 (BTSEL)
unnamed: LED1.A, R14.1
unnamed: LED1.C, R60.1
unnamed: LED2.C, R15.2
unnamed: R60.2, U3.7 (LED/GPIO0)
unnamed 79: U1.85 (PK4(ADC12/PCINT20)); also elsewhere on the board
unnamed: R16.1, U6.23 (SDO(XM))
unnamed: R34.1, U6.22 (SDO(G))
unnamed: LED7.A, U1.25 ((OC1B/PCINT6)PB6)
unnamed: LED7.C, R40.2
unnamed: LED8.A, U1.27 (PH7(T4))
unnamed: LED8.C, R41.1
unnamed: LED9.A, U1.28 ((TOSC2)PG3)
unnamed: LED10.A, U1.29 ((TOSC1)PG4)
unnamed: LED10.C, R42.2
unnamed: LED9.C, R43.2
unnamed: C54.1, L6.2, U$23.P$1
unnamed: L6.1, U$3.1 (ANT)
PWDN_ISL: U1.12 (PH0(RXD2))
RADIO_CS_3.3: U$1.6 (3Y), U$3.13 (NSEL)
RADIO_CS_5.0: U1.19 ((SS/PCINT0)PB0), U$1.7 (3A)
RESET: U1.30 (RESET), U$50.7
RESET_ADS: U1.17 (PH5(OC4C)); also elsewhere on the board
RX: U1.45 ((RXD1/INT2)PD2), U3.44 (TXD0)
RX0: U1.2 ((RXD0/PCIN8)PE0), U$50.10
SCK_3.3: U2.SCLK (SCK), U$1.4 (2Y), U$3.12 (SCLK)
SCK_5.0: U1.20 ((SCK/PCINT1)PB1), U$1.5 (2A), U$50.6; also elsewhere on the board
SCL_3.3: R4.1, U4.2 (SCL1), U6.21 (SCL), U7.4 (SCL), U9.4 (SCL)
SCL_5.0: R7.1, U1.43 ((SCL/INT0)PD0), U4.6 (SCL2)
SDA_3.3: R5.1, U4.3 (SDA1), U6.24 (SDA), U7.6 (SDA), U9.6 (SDA)
SDA_5.0: R8.1, U1.44 ((SDA/INT1)PD1), U4.5 (SDA2)
SD_CS_3.3: U2.CS, U$1.12 (5Y)
SD_CS_5.0: U1.18 (PH6(OC2B)), U$1.11 (5A)
SET: U1.97 ((ADC0)PF0); also elsewhere on the board
SHDN_3.3: R2.2, U$1.10 (4Y), U$3.15 (SDN)
SHDN_5.0: U1.1 ((OC0B)PG5), U$1.9 (4A)
START_ADS: U1.13 (PH1(TXD2)); also elsewhere on the board
TEMP_SENSE: U1.76 ((AD2)PA2), U$24.4 (DQ), U$25.4 (DQ), U$47.4 (DQ), U$48.4 (DQ)
TX: Q3.3 (D), R22.1, U1.46 ((TXD1/INT3)PD3)
TX0: U1.3 ((TXD0)PE1), U$50.9
VCC_GPS: C4.2, C73.1, C74.1, C75.1, L1.2, R10.2, R14.2, T1.1 (D), T1.2 (D), T1.5 (D), T1.6 (D), U3.2 (VCC), U3.36 (REGEN), U3.58 (VCC)

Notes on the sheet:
Microcontroller
Level Converters
Sensors
Data Handling

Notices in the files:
parts and their libraries:
SparkFun-Connectors: Licensing: Creative Commons ShareAlike 4.0 International - https://creativecommons.org/licenses/by-sa/4.0
Wurth_Elektronik_Electromechanic_Input-O: Copyright: Würth Elektronik
